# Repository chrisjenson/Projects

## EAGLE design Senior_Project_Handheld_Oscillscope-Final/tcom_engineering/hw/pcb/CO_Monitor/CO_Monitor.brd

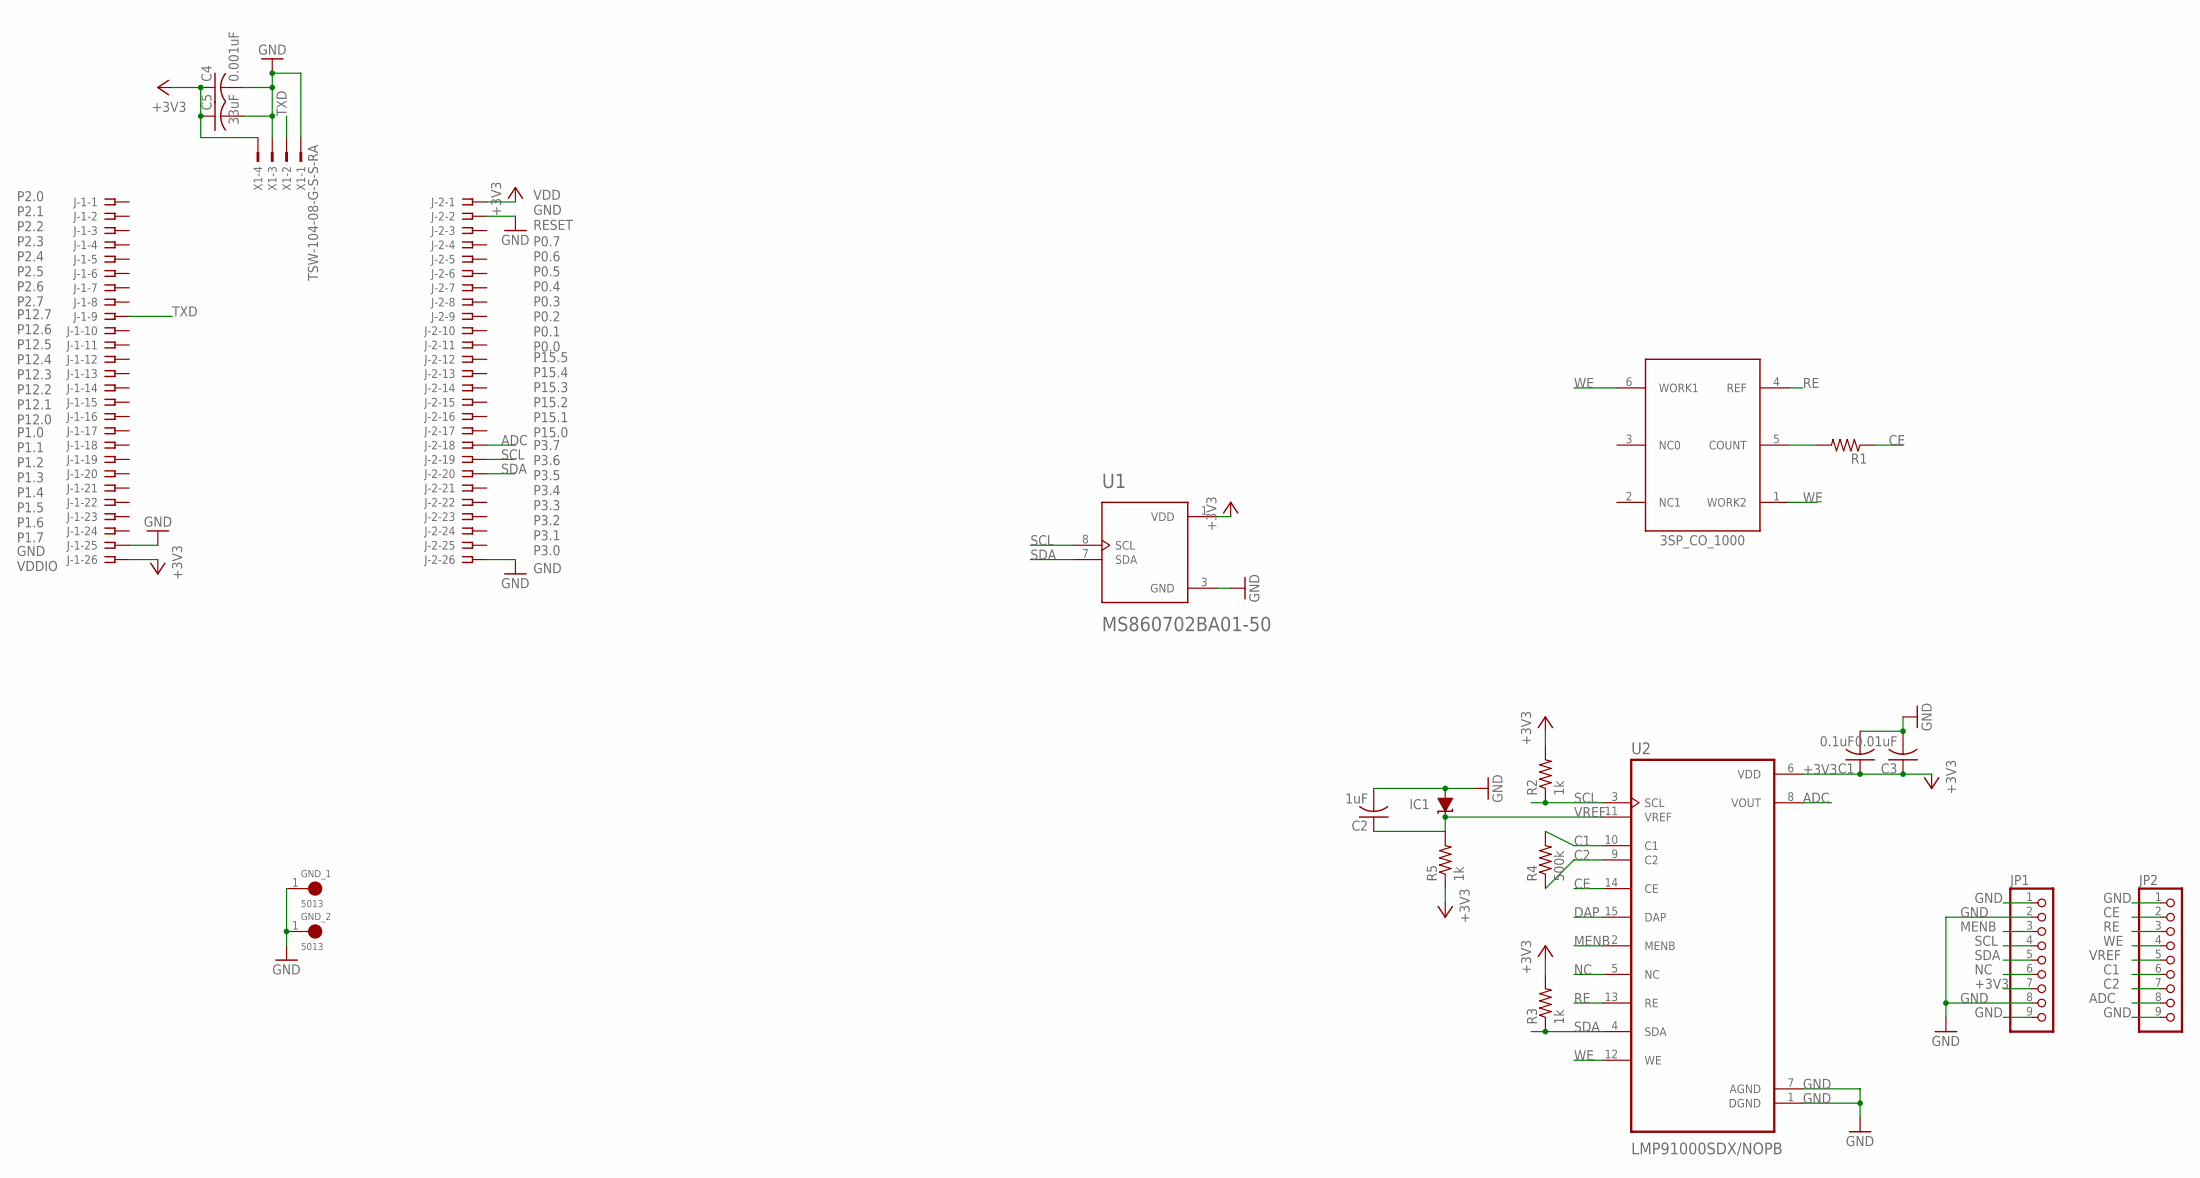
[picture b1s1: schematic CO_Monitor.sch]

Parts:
C1: 0.1uF; C050-025X075
C2: 1uF; C050-025X075
C3: 0.01uF; C050-025X075
C4: 0.001uF; C050-025X075
C5: 33uF; C050-025X075
GND_1, GND_2: 5013; TESTPOINT_5013
IC1: LM4041D12LP; LP_O-PBCY-W3
J-1, J-2: SSW-126-02-G-S
JP1, JP2: PINHD-1X9; 1X09
R1: 50; 0207/10
R2, R3, R5: 1k; 0207/10
R4: 500k; 0207/10
U1: MS860702BA01-50; TE_MS860702BA01-50
U2: LMP91000SDX/NOPB; SON50P400X400X80-15N
U$1: 3SP_CO_1000
X1: TSW-104-08-G-S-S-RA; TSW-104-08-G-S-RA

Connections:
+3V3: C1.1, C3.1, C4.1, C5.1, J-1.26, J-2.1, JP1.7, R2.2, R3.2, R5.1, U1.1 (VDD), U2.6 (VDD), X1.4
ADC: J-2.18, JP2.8, U2.8 (VOUT)
C1: JP2.6, R4.2, U2.10 (C1)
C2: JP2.7, R4.1, U2.9 (C2)
CE: JP2.2, R1.1, U2.14 (CE)
DAP: U2.15 (DAP)
GND: C1.2, C2.2, C3.2, C4.2, C5.2, GND_1.1, GND_2.1, IC1.3 (A), J-1.25, J-2.2, J-2.26, JP1.1, JP1.2, JP1.8, JP1.9, JP2.1, JP2.9, U1.3 (GND), U2.1 (DGND), U2.7 (AGND), X1.1, X1.3
MENB: JP1.3, U2.2 (MENB)
unnamed: R1.2, U$1.5 (COUNT)
NC: JP1.6, U2.5 (NC)
RE: JP2.3, U2.13 (RE), U$1.4 (REF)
SCL: J-2.19, JP1.4, R2.1, U1.8 (SCL), U2.3 (SCL)
SDA: J-2.20, JP1.5, R3.1, U1.7 (SDA), U2.4 (SDA)
TXD: J-1.9, X1.2
VREF: C2.1, IC1.2 (C), JP2.5, R5.2, U2.11 (VREF)
WE: JP2.4, U2.12 (WE), U$1.1 (WORK2), U$1.6 (WORK1)

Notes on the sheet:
P2.0 P2.1 P2.2 P2.3 P2.4 P2.5 P2.6 P2.7
P12.7 P12.6 P12.5 P12.4 P12.3 P12.2 P12.1 P12.0
P1.0 P1.1 P1.2 P1.3 P1.4 P1.5 P1.6 P1.7
GND VDDIO
GND
P3.7 P3.6 P3.5 P3.4 P3.3 P3.2 P3.1 P3.0
P15.5 P15.4 P15.3 P15.2 P15.1 P15.0
P0.7 P0.6 P0.5 P0.4 P0.3 P0.2 P0.1 P0.0
VDD GND RESET

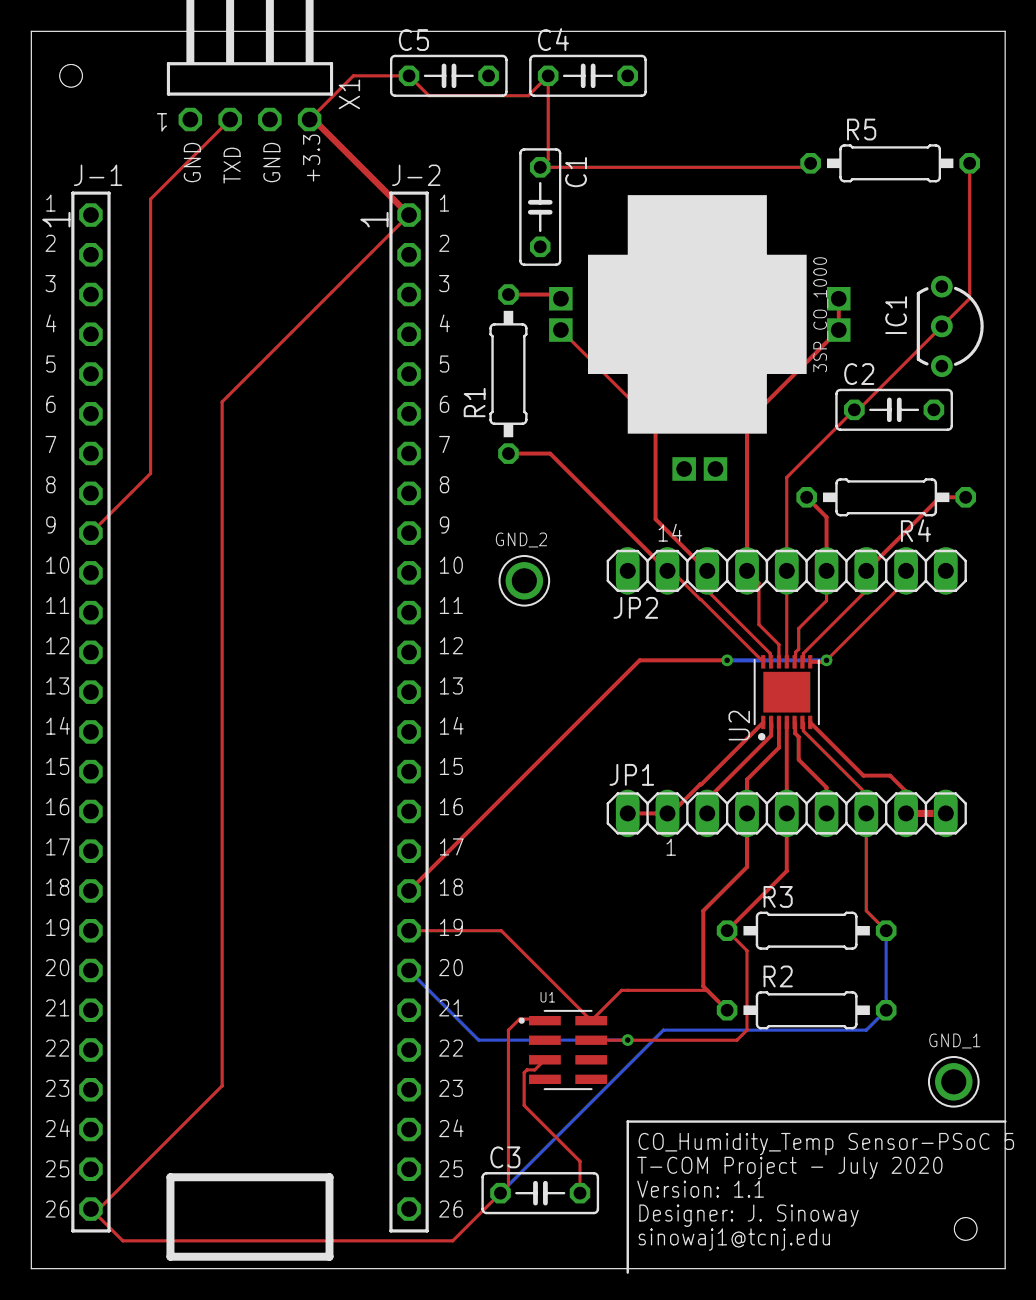
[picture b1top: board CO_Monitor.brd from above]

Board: 2 copper layers, 62.2 x 79.0 mm, 21 parts (0 on the bottom side), 15 nets.

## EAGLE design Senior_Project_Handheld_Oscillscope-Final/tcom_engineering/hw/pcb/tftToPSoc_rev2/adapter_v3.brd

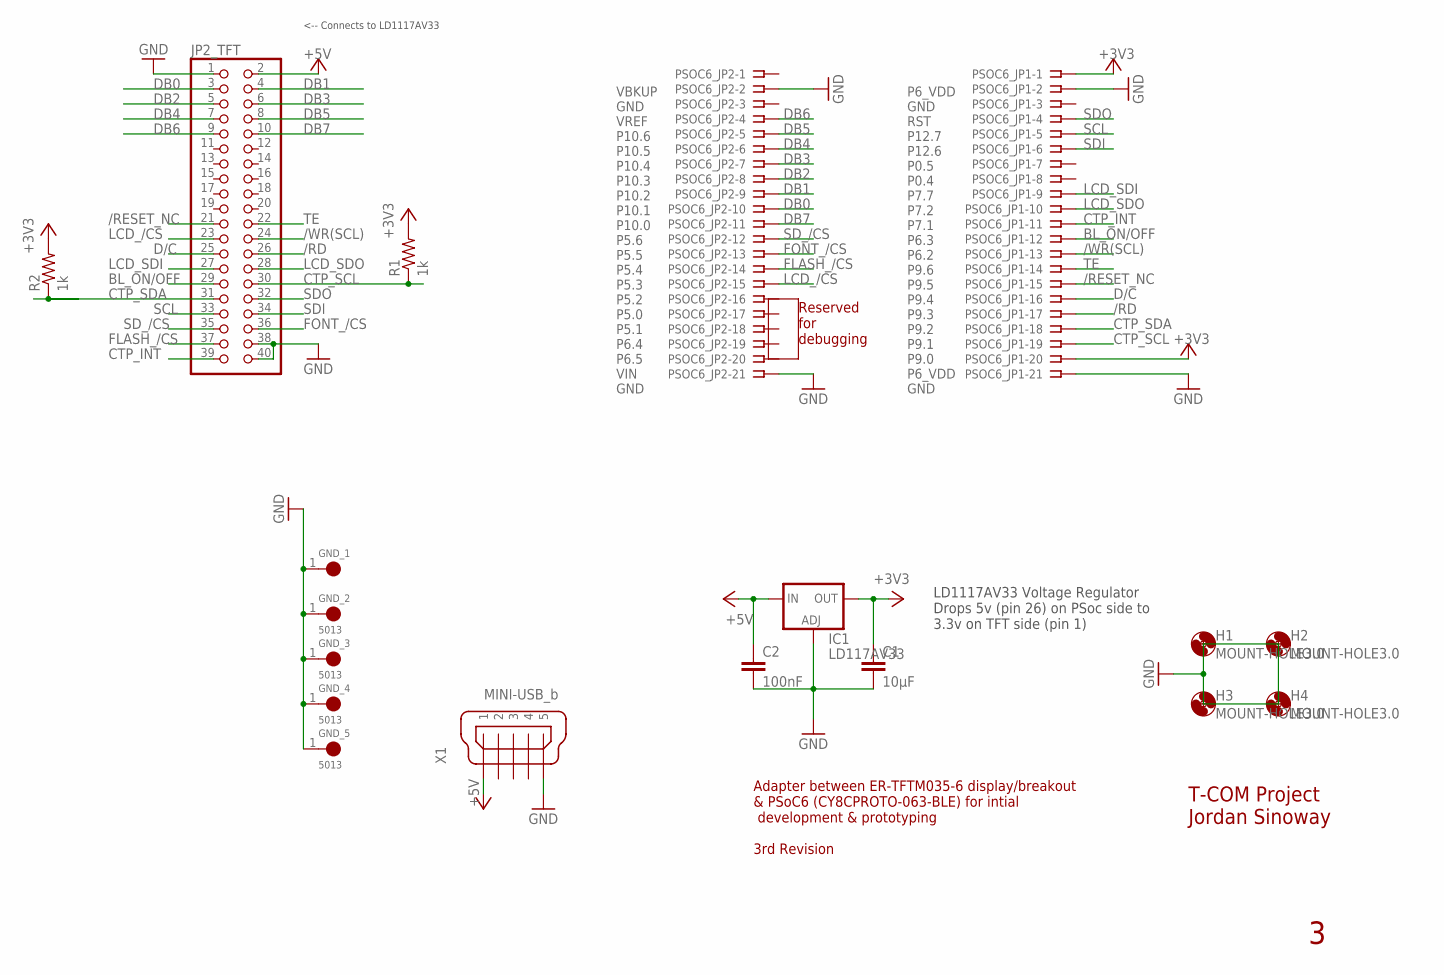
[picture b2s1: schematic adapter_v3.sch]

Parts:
C1: 10μF; C2.5-2
C2: 100nF; C2.5-2
GND_1, GND_2, GND_3, GND_4, GND_5: 5013; TESTPOINT_5013
H1, H2, H3, H4: MOUNT-HOLE3.0; 3,0
IC1: LD117AV33; TO220L1
JP2_TFT: PINHD-2X20; 2X20
PSOC6_JP1, PSOC6_JP2: SSW-121-02-G-S
R1, R2: 1k; 0204/7
X1: MINI-USB_b; 32005-601

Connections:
+3V3: C1.1, IC1.2 (OUT), PSOC6_JP1.1, PSOC6_JP1.20, R1.2, R2.2
+5V: C2.1, IC1.3 (IN), JP2_TFT.2, X1.1
/RD: JP2_TFT.26, PSOC6_JP1.17
/RESET_NC: JP2_TFT.21, PSOC6_JP1.15
/WR(SCL): JP2_TFT.24, PSOC6_JP1.13
BL_ON/OFF: JP2_TFT.29, PSOC6_JP1.12
CTP_INT: JP2_TFT.39, PSOC6_JP1.11
CTP_SCL: JP2_TFT.30, PSOC6_JP1.19, R1.1
CTP_SDA: JP2_TFT.31, PSOC6_JP1.18, R2.1
D/C: JP2_TFT.25, PSOC6_JP1.16
DB0: JP2_TFT.3, PSOC6_JP2.10
DB1: JP2_TFT.4, PSOC6_JP2.9
DB2: JP2_TFT.5, PSOC6_JP2.8
DB3: JP2_TFT.6, PSOC6_JP2.7
DB4: JP2_TFT.7, PSOC6_JP2.6
DB5: JP2_TFT.8, PSOC6_JP2.5
DB6: JP2_TFT.9, PSOC6_JP2.4
DB7: JP2_TFT.10, PSOC6_JP2.11
FLASH_/CS: JP2_TFT.37, PSOC6_JP2.14
FONT_/CS: JP2_TFT.36, PSOC6_JP2.13
GND: C1.2, C2.2, GND_1.1, GND_2.1, GND_3.1, GND_4.1, GND_5.1, IC1.1 (ADJ), JP2_TFT.1, JP2_TFT.38, JP2_TFT.40, PSOC6_JP1.2, PSOC6_JP1.21, PSOC6_JP2.2, PSOC6_JP2.21, X1.5
LCD_/CS: JP2_TFT.23, PSOC6_JP2.15
LCD_SDI: JP2_TFT.27, PSOC6_JP1.9
LCD_SDO: JP2_TFT.28, PSOC6_JP1.10
SCL: JP2_TFT.33, PSOC6_JP1.5
SDI: JP2_TFT.34, PSOC6_JP1.6
SDO: JP2_TFT.32, PSOC6_JP1.4
SD_/CS: JP2_TFT.35, PSOC6_JP2.12
TE: JP2_TFT.22, PSOC6_JP1.14

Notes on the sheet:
LD1117AV33 Voltage Regulator Drops 5v (pin 26) on PSoc side to 3.3v on TFT side (pin 1)
<-- Connects to LD1117AV33
T-COM Project Jordan Sinoway
Adapter between ER-TFTM035-6 display/breakout & PSoC6 (CY8CPROTO-063-BLE) for intial development & prototyping 3rd Revision
VBKUP GND VREF P10.6 P10.5 P10.4 P10.3 P10.2 P10.1 P10.0 P5.6 P5.5 P5.4 P5.3 P5.2 P5.0 P5.1 P6.4 P6.5 VIN GND
P6_VDD GND RST P12.7 P12.6 P0.5 P0.4 P7.7 P7.2 P7.1 P6.3 P6.2 P9.6 P9.5 P9.4 P9.3 P9.2 P9.1 P9.0 P6_VDD GND
Reserved for debugging

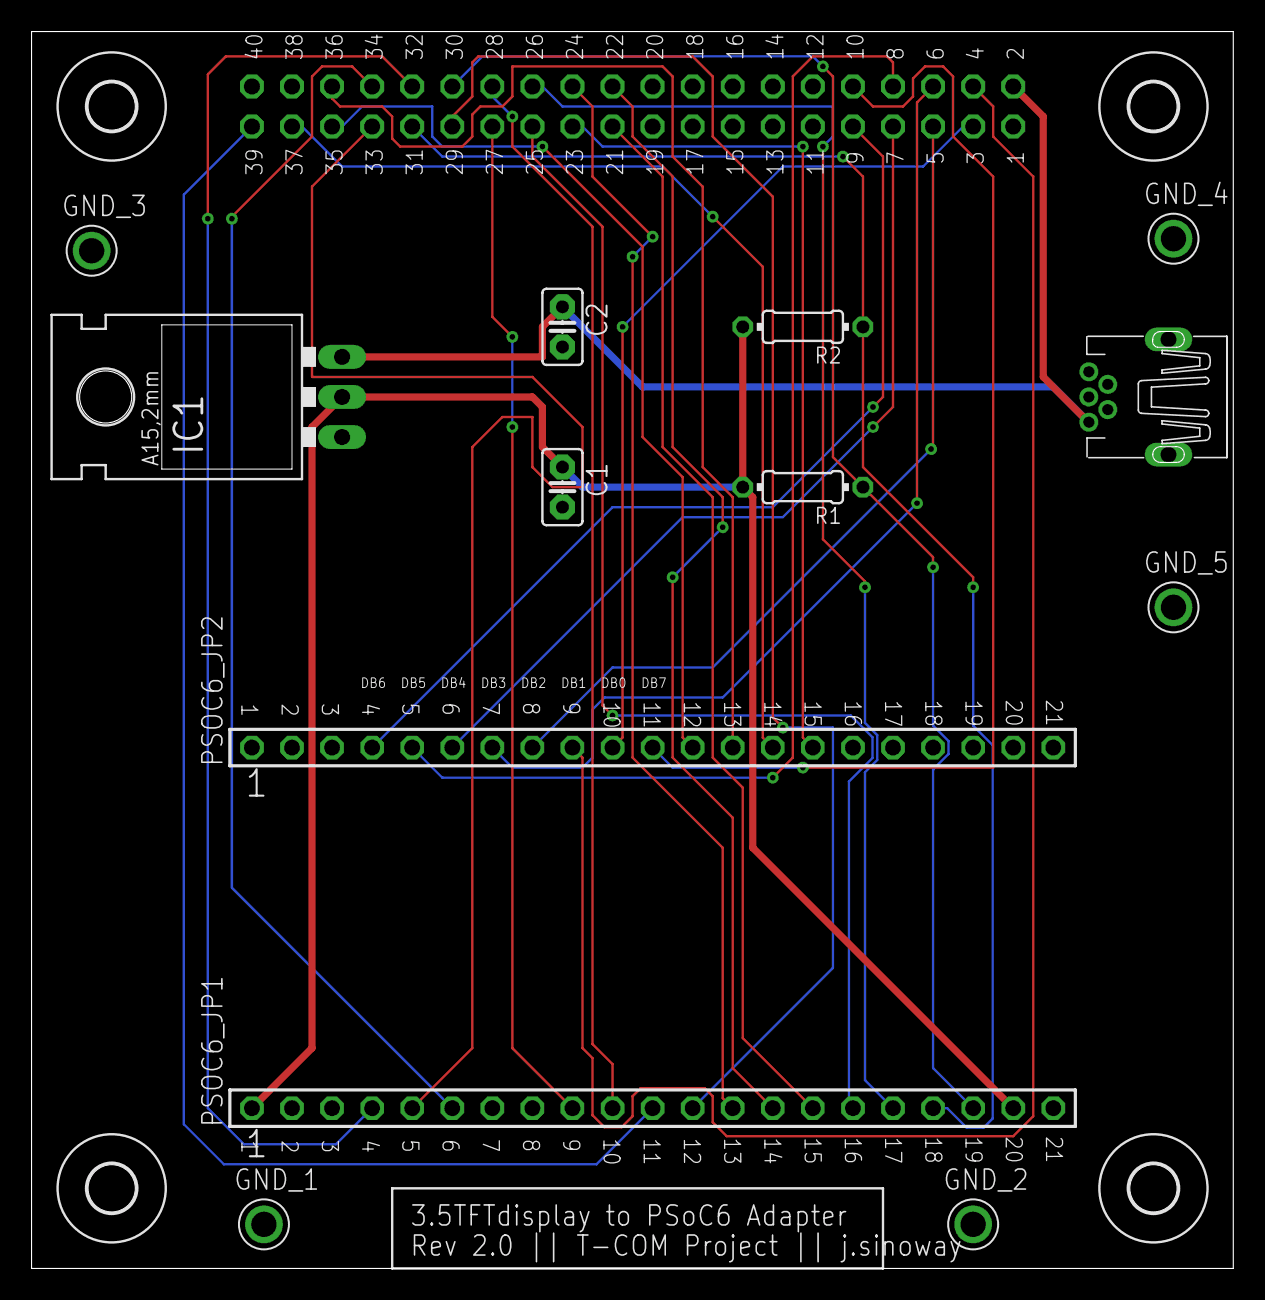
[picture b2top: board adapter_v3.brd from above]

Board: 2 copper layers, 76.2 x 78.4 mm, 18 parts (1 on the bottom side), 29 nets.
